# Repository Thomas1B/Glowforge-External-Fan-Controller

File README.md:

# Glowforge External Fan Controller

**Note: This will avoid any warranty of glowforge**

This program is designed to read the voltage from the fan pin on the Glowforge laser cutter. When the pin is high, a relay is turned on to run an exhaust fan. After the voltage drops back to 0, the fan runs for a little longer to allow for better exhaust of fumes.

## Components

To make the controller the following components are needed:<br>
1. Attiny85.
2. 5V Regulator.
3. AC Relay, with activation voltage of 3.3V or 5V.
4. Red led.
5. Green led.
6. 10K Resistor.
7. 2 x Resistor for LEDs (depends on brightness).
8. Diode.
9. 10uF Capacitor.
10. 22uF Capacitor.
11. Momentary Push Button.
12. Slide Switch.
13. Terminal Block.
14. JST Connector.
15. Pin Headers.

Also needed is some arduino board to program the attiny85.

DigiKey (https://www.digikey.ca/) is a great place to buy electronics from.

The attiny85 is very small microcontroller, convienent for simple projects. The AC relay is used to run an external exhaust fan when the controller senses high voltage. The red led is used to notify that the controller has power, and the green is show that relay should be running (which is useful for debugging if the fan should be run and it's not). The button is used a reset and the switch is used to manually active the relay.

## Diagrams

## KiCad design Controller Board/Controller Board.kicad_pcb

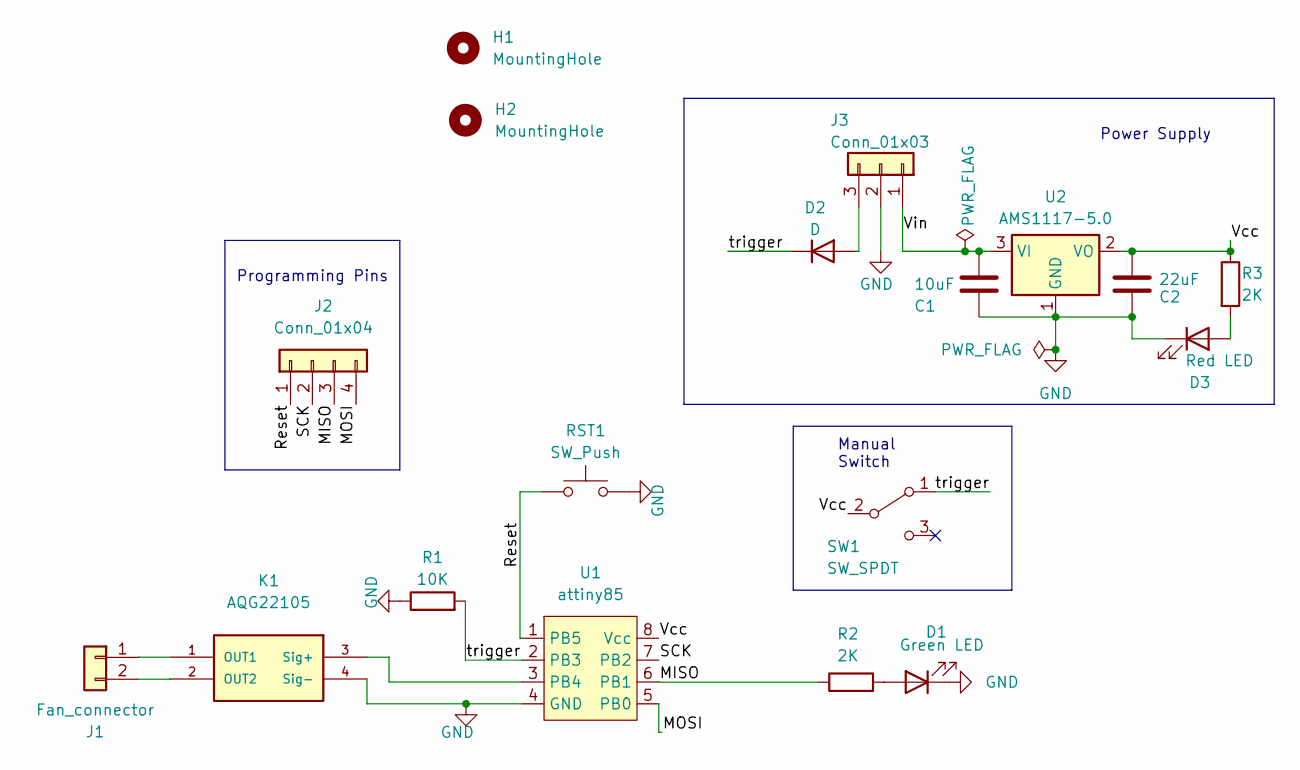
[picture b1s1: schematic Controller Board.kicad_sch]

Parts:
C1: 10uF; C_0805_2012Metric_Pad1.18x1.45mm_HandSolder
C2: 22uF; C_0805_2012Metric_Pad1.18x1.45mm_HandSolder
D1: Green LED; LED_0805_2012Metric_Pad1.15x1.40mm_HandSolder
D2: D; Diode-SOD-80
D3: Red LED; LED_0805_2012Metric_Pad1.15x1.40mm_HandSolder
H1, H2: MountingHole; MountingHole_3.2mm_M3
J1: Fan_connector; myTerminalBlock-2_P5.08mm
J2: Conn_01x04; PinHeader_1x04_P2.54mm_Vertical
J3: Conn_01x03; JST_XH_B3B-XH-A_1x03_P2.50mm_Vertical
K1: AQG22105; RELAY_AQG22105
R1: 10K; R_0805_2012Metric_Pad1.20x1.40mm_HandSolder
R2, R3: 2K; R_0805_2012Metric_Pad1.20x1.40mm_HandSolder
RST1: SW_Push; SW_PTS636_SM43J_SMTR_LFS
SW1: SW_SPDT; EG1218 Slide Switch
U1: attiny85; DIP-8_W7.62mm
U2: AMS1117-5.0; SOT-223-3_TabPin2

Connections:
/MISO: J2.3, R2.1, U1.6 (PB1)
/MOSI: J2.4, U1.5 (PB0)
/Reset: J2.1, RST1.2, U1.1 (PB5)
/SCK: J2.2, U1.7 (PB2)
/Vcc: C2.2, R3.1, SW1.2 (B), U1.8 (Vcc), U2.2 (VO)
/Vin: C1.2, J3.1, U2.3 (VI)
/trigger: D2.1 (K), R1.2, SW1.1 (A), U1.2 (PB3)
GND: C1.1, C2.1, D1.1 (K), D3.1 (K), J3.2, K1.4 (Sig-), R1.1, RST1.1, U1.4 (GND), U2.1 (GND)
unnamed: D1.2 (A), R2.2
unnamed: D2.2 (A), J3.3
unnamed: D3.2 (A), R3.2
unnamed: J1.1, K1.1 (OUT1)
unnamed: J1.2, K1.2 (OUT2)
unnamed: K1.3 (Sig+), U1.3 (PB4)

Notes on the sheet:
Power Supply
Manual Switch
Programming Pins

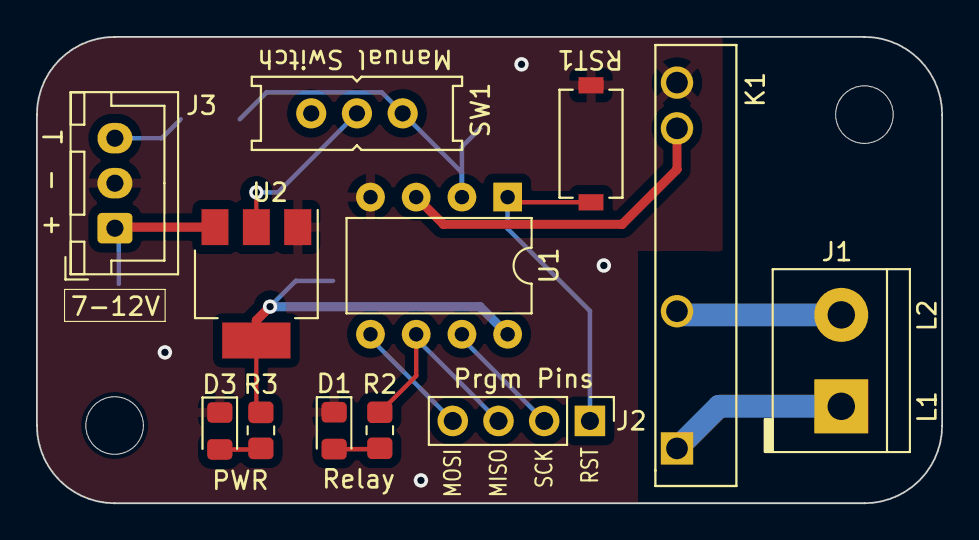
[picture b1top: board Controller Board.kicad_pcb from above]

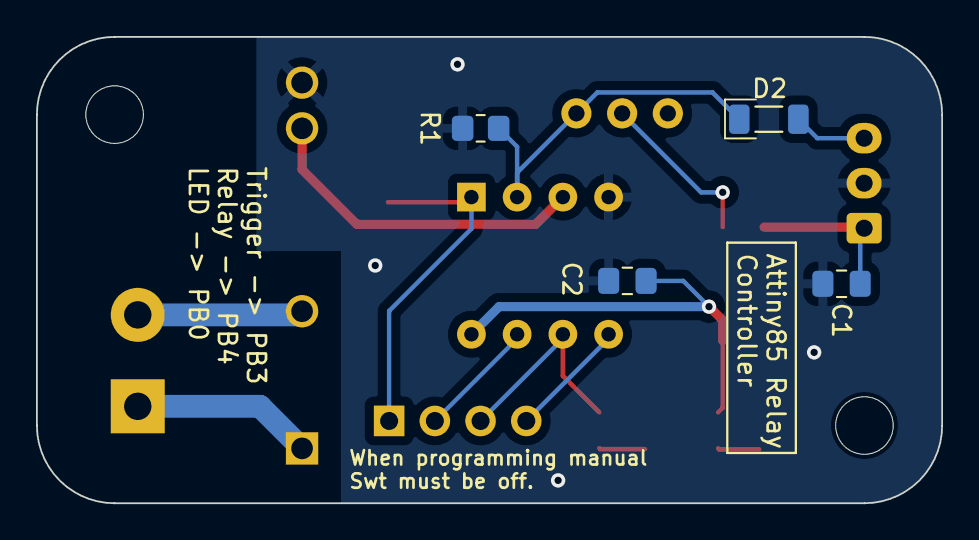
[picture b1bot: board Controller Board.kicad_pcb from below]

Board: 2 copper layers, 50.3 x 25.9 mm, 18 parts (4 on the bottom side), 14 nets.

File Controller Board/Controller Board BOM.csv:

"Project:","Controller Board\Controller Board.kicad_sch"
"Date:","9/28/2023"
"Tool:","Eeschema 7.0.6"
"BOM Generator:","myScripts\myKiCad_BOM_Maker.py"

"Total Component Count:","18"
"Component Type Count:","16"
"Ref","Qnty","Value","Description","Cmp name","Footprint"

"Component: 1/16:"
"C1","1","10uF","Unpolarized capacitor","C","Capacitor_SMD:C_0805_2012Metric_Pad1.18x1.45mm_HandSolder"

"Component: 2/16:"
"C2","1","22uF","Unpolarized capacitor","C","Capacitor_SMD:C_0805_2012Metric_Pad1.18x1.45mm_HandSolder"

"Component: 3/16:"
"D1","1","Green LED","Light emitting diode","LED","LED_SMD:LED_0805_2012Metric_Pad1.15x1.40mm_HandSolder"

"Component: 4/16:"
"D2","1","D","Diode","D","0_Thomas_Footprints:Diode-SOD-80"

"Component: 5/16:"
"D3","1","Red LED","Light emitting diode","LED","LED_SMD:LED_0805_2012Metric_Pad1.15x1.40mm_HandSolder"

"Component: 6/16:"
"H1, H2","2","MountingHole","Mounting Hole without connection","MountingHole","MountingHole:MountingHole_3.2mm_M3"

"Component: 7/16:"
"J1","1","Fan_connector","Generic connector, single row, 01x02","Conn_01x02","0_Thomas_Footprints:myTerminalBlock-2_P5.08mm"

"Component: 8/16:"
"J2","1","Conn_01x04","Generic connector, single row, 01x04","Conn_01x04","Connector_PinHeader_2.54mm:PinHeader_1x04_P2.54mm_Vertical"

"Component: 9/16:"
"J3","1","Conn_01x03","Generic connector, single row, 01x03","Conn_01x03","Connector_JST:JST_XH_B3B-XH-A_1x03_P2.50mm_Vertical"

"Component: 10/16:"
"K1","1","AQG22105","SS Relay, 5V trig, 250AC 2A","AQG22105 Relay","0_Thomas_Footprints:RELAY_AQG22105"

"Component: 11/16:"
"R1","1","10K","Resistor","R","Resistor_SMD:R_0805_2012Metric_Pad1.20x1.40mm_HandSolder"

"Component: 12/16:"
"R2, R3","2","2K","Resistor","R","Resistor_SMD:R_0805_2012Metric_Pad1.20x1.40mm_HandSolder"

"Component: 13/16:"
"RST1","1","SW_Push","Push button switch, generic, two pins","SW_Push","0_Thomas_Footprints:SW_PTS636_SM43J_SMTR_LFS"

"Component: 14/16:"
"SW1","1","SW_SPDT","Switch, single pole double throw","SW_SPDT","0_Thomas_Footprints:EG1218 Slide Switch"

"Component: 15/16:"
"U1","1","attiny85","ATtiny85","ATTINY85","Package_DIP:DIP-8_W7.62mm"

"Component: 16/16:"
"U2","1","AMS1117-5.0","1A Low Dropout regulator, positive, 5.0V fixed output, SOT-223","AMS1117-5.0","Package_TO_SOT_SMD:SOT-223-3_TabPin2"

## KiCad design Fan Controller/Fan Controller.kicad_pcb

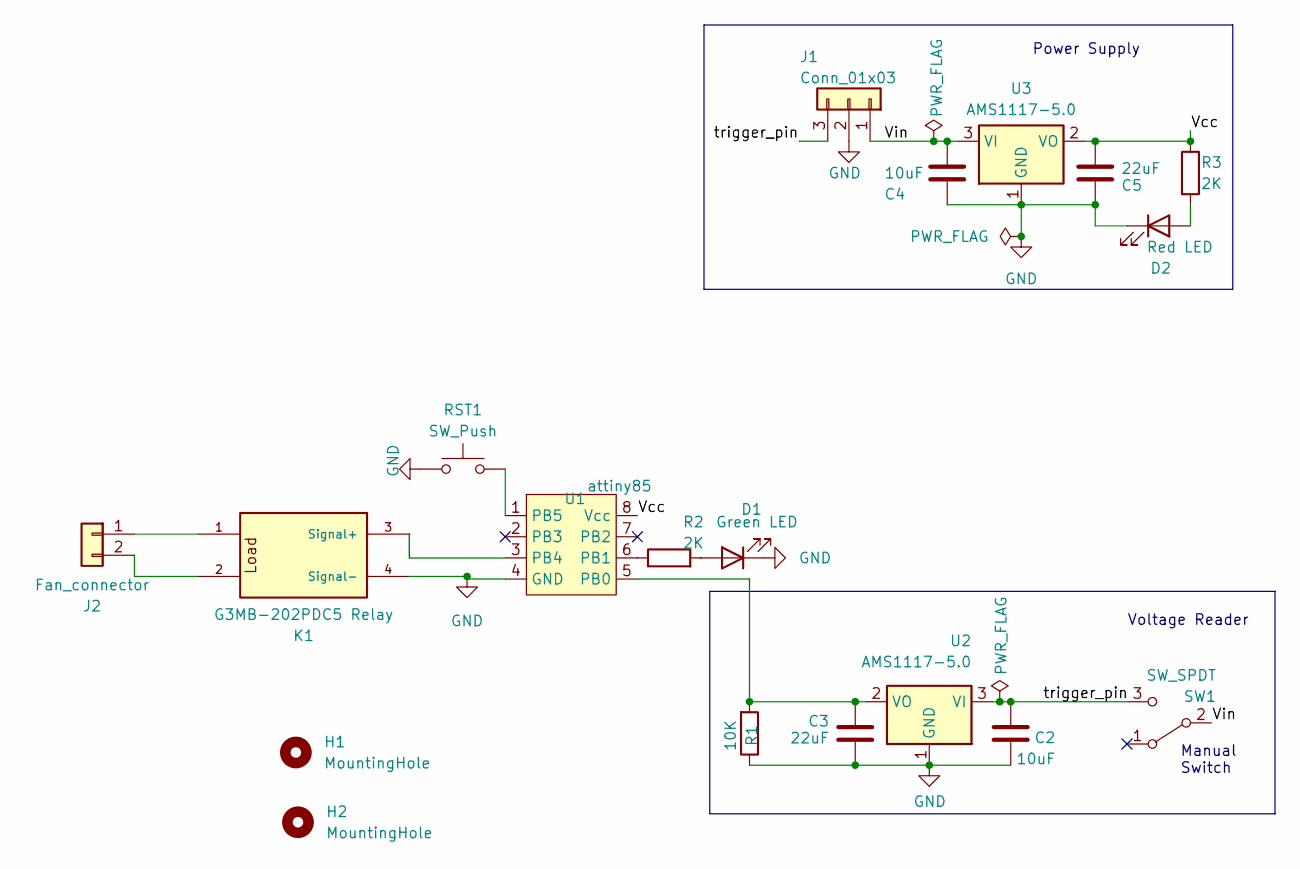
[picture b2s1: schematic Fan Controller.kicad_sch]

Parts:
C2, C4: 10uF; C_0805_2012Metric_Pad1.18x1.45mm_HandSolder
C3, C5: 22uF; C_0805_2012Metric_Pad1.18x1.45mm_HandSolder
D1: Green LED; LED_0805_2012Metric_Pad1.15x1.40mm_HandSolder
D2: Red LED; LED_0805_2012Metric_Pad1.15x1.40mm_HandSolder
H1, H2: MountingHole; MountingHole_2.2mm_M2
J1: Conn_01x03; JST_XH_B3B-XH-A_1x03_P2.50mm_Vertical
J2: Fan_connector; myTerminalBlock-2_P5.08mm
K1: G3MB-202PDC5 Relay; PARTREV J091-E1-1A
R1: 10K; R_0805_2012Metric_Pad1.20x1.40mm_HandSolder
R2, R3: 2K; R_0805_2012Metric_Pad1.20x1.40mm_HandSolder
RST1: SW_Push; SW_PTS636_SM43J_SMTR_LFS
SW1: SW_SPDT; EG1218 Slide Switch
U1: attiny85; DIP-8_W7.62mm
U2, U3: AMS1117-5.0; SOT-223-3_TabPin2

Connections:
/Vcc: C5.2, R3.1, U1.8 (Vcc), U3.2 (VO)
/Vin: C4.2, J1.1, SW1.2 (B), U3.3 (VI)
/trigger_pin: C2.1, J1.3, SW1.3 (C), U2.3 (VI)
GND: C2.2, C3.2, C4.1, C5.1, D1.1 (K), D2.1 (K), J1.2, K1.4 (Signal-), R1.1, RST1.1, U1.4 (GND), U2.1 (GND), U3.1 (GND)
unnamed: D1.2 (A), R2.2
unnamed: D2.2 (A), R3.2
unnamed: J2.1, K1.1
unnamed: J2.2, K1.2
unnamed: K1.3 (Signal+), U1.3 (PB4)
unnamed: C3.1, R1.2, U1.5 (PB0), U2.2 (VO)
unnamed: R2.1, U1.6 (PB1)
unnamed: RST1.2, U1.1 (PB5)

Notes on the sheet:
Power Supply
Manual Switch
Voltage Reader

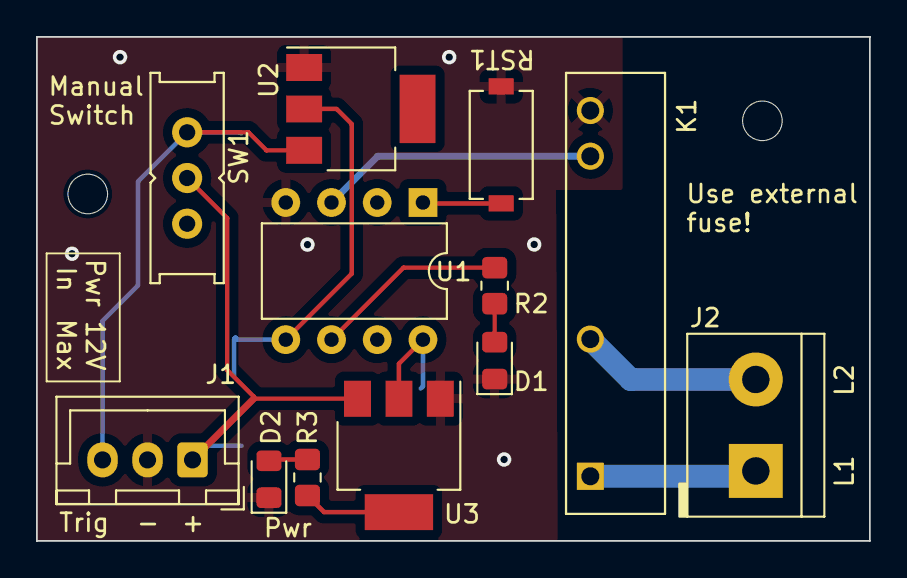
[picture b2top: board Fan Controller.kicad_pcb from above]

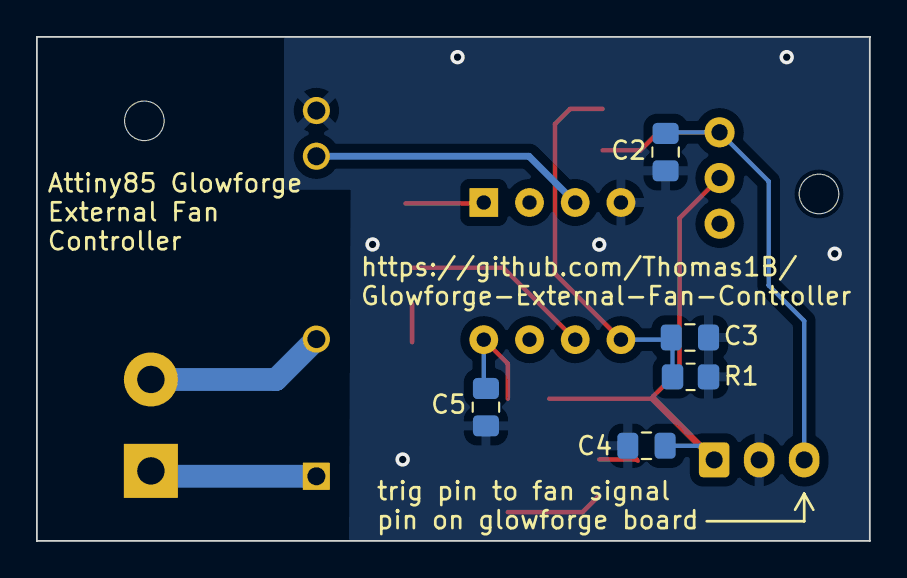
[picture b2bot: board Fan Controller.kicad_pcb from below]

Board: 2 copper layers, 46.3 x 28.0 mm, 19 parts (5 on the bottom side), 12 nets.

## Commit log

2023-08-22 add program code
2023-08-22 Create LICENSE
2023-08-23 added comments
2023-08-23 created KiCad files
2023-08-29 updated program
2023-08-29 updated schematic
2023-08-30 created final Schematic and PCB
2023-08-30 add Screenshot of schematic
2023-08-30 final verison
2023-09-05 final Schematic
2023-09-28 syncing
2023-09-29 final version
2023-10-02 removed files around
2023-10-05 changed extra runtime
